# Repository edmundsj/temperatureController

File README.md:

# TEC Temperature Controller PCB
This PCB is designed to monitor and control the temperature of an object heated or cooled with a thermoelectric cooler (TEC), and is capable of driving up to 8A

## Features
- TEC temperature regulation within 0.1C using PI control
- Max TEC Voltage/current of 3.6V/6A when powered off 5V
- 1% settling time of ~90s 
- Bidirectional temp. control (heating and cooling) 
- 6A max current with 8-bit current monitoring (~25mA accuracy)
- Computer-independent measurement and temperature control using on-board interface
- Can be powered over USB (current limited by driving source)
- Closed-loop control of temperature using MCP9808 remote temperature sensor
- Two 3-digit 7-segment displays for temperature setpoint and measured value
- Knob potentiometer for setting target temperature
- Passive cooling (~4K/W thermal resistance) with 1.5" radial heatsink
- Arduino nano-based

Fully populated PCB

Unpopulated, as-fabricated PCB

## Getting Started
Kicad design files for this PCB are located in the ``kicad/`` folder. Gerbers
can be generated directly for fabrication, or you can find the latest gerbers
in the ``gerbers/`` directory. The parts required can be found in ``bom.csv``.
Software can be found in the ``controller_software/`` directory, which can be
copied to your local machine, and uploaded to an Arduino nano via the Arduino
IDE. This system is rated to work at 5V, so make sure the power adapter used is
rated for 5V, and as much current as is required. For the TEC I built this
system around, that is ~6A.

## Issues
### Issues in Version 1
- [FIXED v2] Need VDD, GND connections on header going to MCP9808 board in addition to SDA and SCL.
- [FIXED v2] Need to make sure the ordering and connector matches that of the device PCB.
- [FIXED v2] In the future, a couple of accessible header GND connections would be nice, even just for probing.
- [FIXED v2] Should edit the silkscreen to include the directionality of the Arduino Nano's USB. 
- [FIXED v2] Should swap out MOSFET for a more linear BJT
- [FIXED v2] Swap out MOSFET for transistor with much lower thermal resistance
- [FIXED v2] My choice of resistor is not sufficient, the thing heats up and starts to smoke after a couple seconds at ~5A. 

### Issues in Version 2
- [FIXED v3] R4 is too close to the heatsink, difficult to access. Moved.
- [FIXED v3] Added capacitor for filtering of input drive voltage
- [FIXED v3] Added 2x2 ground header pins for probing
- [FIXED v3] Added relay with drive transistor to allow bidirectional current flow through TEC
- [FIXED v3] Added silkscreen + courtyard + mounting holes for main heatsink
- [FIXED v3] Current sensing is unreliable due to ADC being near rails, added opamp buffer + biasing

### Issues in Version 3
- Standoffs should be as far to the outside to avoid tipping the board when using screw terminals
- Need to add test piont for VDR_F. 
- C4 should be removed. We have no business filtering a voltage going to the base of the BJT.
- Add probe points for communication interface for easier debugging. 
- Add probe points for ground silkscreen
- Decouple VDD of arduino and TEC.

## Acknowledgements

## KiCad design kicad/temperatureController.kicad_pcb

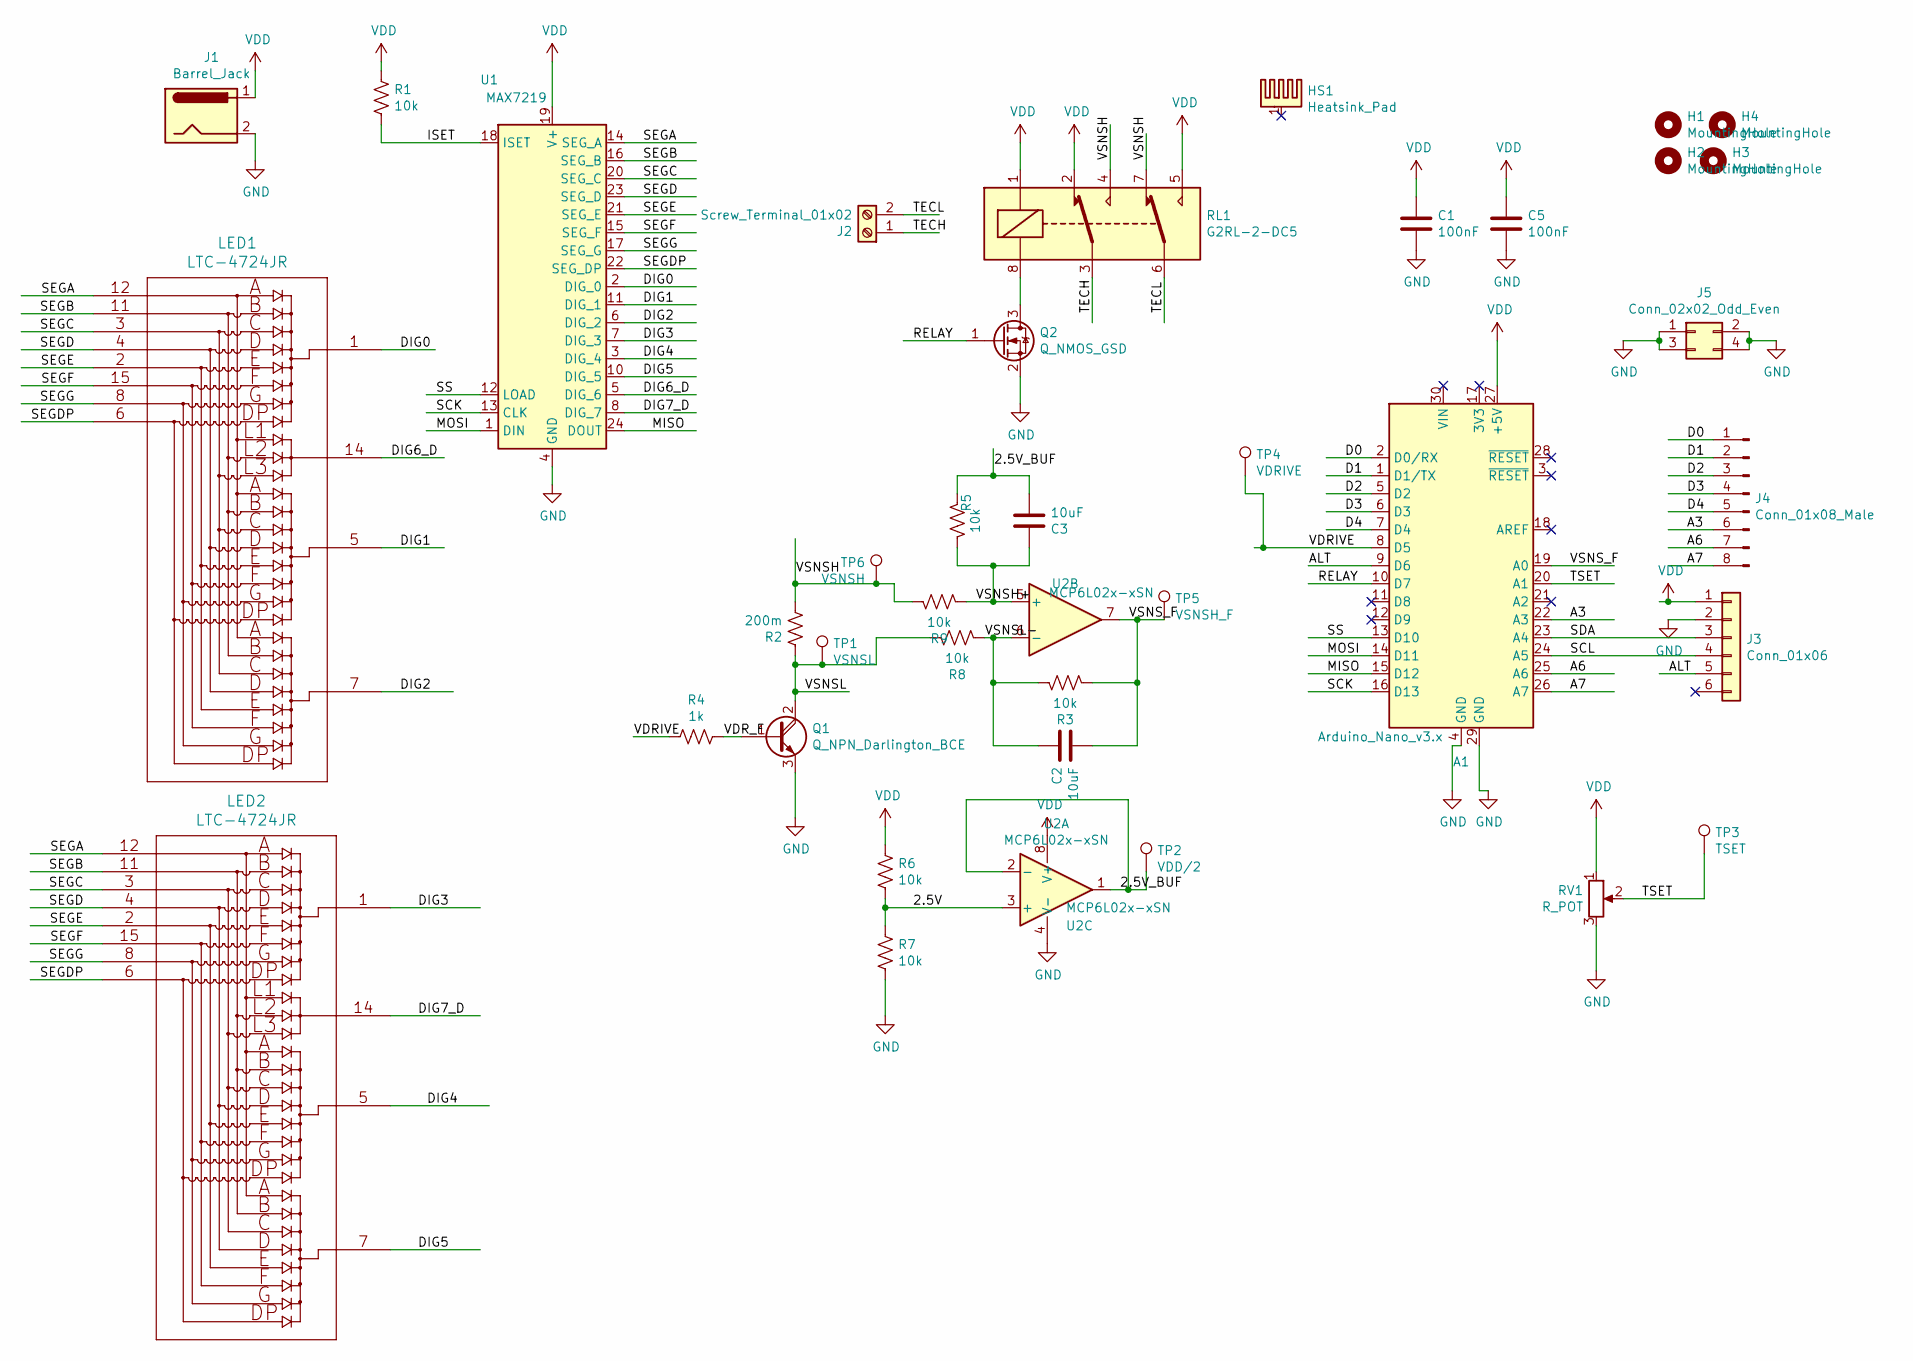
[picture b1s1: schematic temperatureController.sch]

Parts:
A1: Arduino_Nano_v3.x; Arduino_Nano
C1: 100nF; CP_Radial_D10.0mm_P5.00mm
C2, C3: 10uF; C_0805_2012Metric_Pad1.15x1.40mm_HandSolder
C5: 100nF; C_0805_2012Metric_Pad1.15x1.40mm_HandSolder
H1, H2, H3, H4: MountingHole; m3_mounting_hole
HS1: Heatsink_Pad; heatsink
J1: Barrel_Jack; BarrelJack_Horizontal
J2: Screw_Terminal_01x02; TerminalBlock_Altech_AK300-2_P5.00mm
J3: Conn_01x06; S6B-XH-SM4-TB
J4: Conn_01x08_Male; PinHeader_1x08_P2.54mm_Vertical
J5: Conn_02x02_Odd_Even; PinHeader_2x02_P2.54mm_Vertical
LED1, LED2: LTC-4724JR
Q1: Q_NPN_Darlington_BCE; TO-220-3_Vertical
Q2: Q_NMOS_GSD; SOT-323_SC-70_Handsoldering
R1, R3, R5, R6, R7, R8, R9: 10k; R_0805_2012Metric_Pad1.15x1.40mm_HandSolder
R2: 200m; TO-220_resistor
R4: 1k; R_0805_2012Metric_Pad1.15x1.40mm_HandSolder
RL1: G2RL-2-DC5; Relay_DPDT_Omron_G2RL
RV1: R_POT; P120PK_Potentiometer
TP1: VSNSL; TestPoint_Keystone_5000-5004_Miniature
TP2: VDD/2; TestPoint_Keystone_5000-5004_Miniature
TP3: TSET; TestPoint_Keystone_5000-5004_Miniature
TP4: VDRIVE; TestPoint_Keystone_5000-5004_Miniature
TP5: VSNSH_F; TestPoint_Keystone_5000-5004_Miniature
TP6: VSNSH; TestPoint_Keystone_5000-5004_Miniature
U1: MAX7219; SOIC-24W_7.5x15.4mm_P1.27mm
U2: MCP6L02x-xSN; SOIC-8_3.9x4.9mm_P1.27mm

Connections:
/2.5V: R6.2, R7.1, U2.3 (+)
/2.5V_BUF: C3.2, R5.2, TP2.1, U2.1, U2.2 (-)
/A3: A1.22 (A3), J4.6
/A6: A1.25 (A6), J4.7
/A7: A1.26 (A7), J4.8
/ALT: A1.9 (D6), J3.5
/D0: A1.2 (D0/RX), J4.1
/D1: A1.1 (D1/TX), J4.2
/D2: A1.5 (D2), J4.3
/D3: A1.6 (D3), J4.4
/D4: A1.7 (D4), J4.5
/DIG0: LED1.1, U1.2 (DIG_0)
/DIG1: LED1.5, U1.11 (DIG_1)
/DIG2: LED1.7, U1.6 (DIG_2)
/DIG3: LED2.1, U1.7 (DIG_3)
/DIG4: LED2.5, U1.3 (DIG_4)
/DIG5: LED2.7, U1.10 (DIG_5)
/DIG6_D: LED1.14, U1.5 (DIG_6)
/DIG7_D: LED2.14, U1.8 (DIG_7)
/ISET: R1.2, U1.18 (ISET)
/MISO: A1.15 (D12), U1.24 (DOUT)
/MOSI: A1.14 (D11), U1.1 (DIN)
/RELAY: A1.10 (D7), Q2.1 (G)
/SCK: A1.16 (D13), U1.13 (CLK)
/SCL: A1.24 (A5), J3.4
/SDA: A1.23 (A4), J3.3
/SEGA: LED1.12, LED2.12, U1.14 (SEG_A)
/SEGB: LED1.11, LED2.11, U1.16 (SEG_B)
/SEGC: LED1.3, LED2.3, U1.20 (SEG_C)
/SEGD: LED1.4, LED2.4, U1.23 (SEG_D)
/SEGDP: LED1.6, LED2.6, U1.22 (SEG_DP)
/SEGE: LED1.2, LED2.2, U1.21 (SEG_E)
/SEGF: LED1.15, LED2.15, U1.15 (SEG_F)
/SEGG: LED1.8, LED2.8, U1.17 (SEG_G)
/SS: A1.13 (D10), U1.12 (LOAD)
/TECH: J2.1, RL1.3
/TECL: J2.2, RL1.6
/TSET: A1.20 (A1), RV1.2, TP3.1
/VDRIVE: A1.8 (D5), R4.2, TP4.1
/VDR_F: Q1.1 (B), R4.1; also elsewhere on the board
/VSNSH: R2.2, R9.2, RL1.4, RL1.7, TP6.1
/VSNSH+: C3.1, R5.1, R9.1, U2.5 (+)
/VSNSL: Q1.2 (C), R2.1, R8.2, TP1.1
/VSNSL-: C2.1, R3.2, R8.1, U2.6 (-)
/VSNS_F: A1.19 (A0), C2.2, R3.1, TP5.1, U2.7
GND: A1.4 (GND), A1.29 (GND), C1.2, C5.2, J1.2, J3.2, J5.1, J5.2, J5.3, J5.4, Q1.3 (E), Q2.2 (S), R7.2, RV1.3, U1.4 (GND), U1.9 (GND), U2.4 (V-); also elsewhere on the board
unnamed: Q2.3 (D), RL1.8
VDD: A1.27 (+5V), C1.1, C5.1, J1.1, J3.1, R1.1, R6.1, RL1.1, RL1.2, RL1.5, RV1.1, U1.19 (V+), U2.8 (V+)

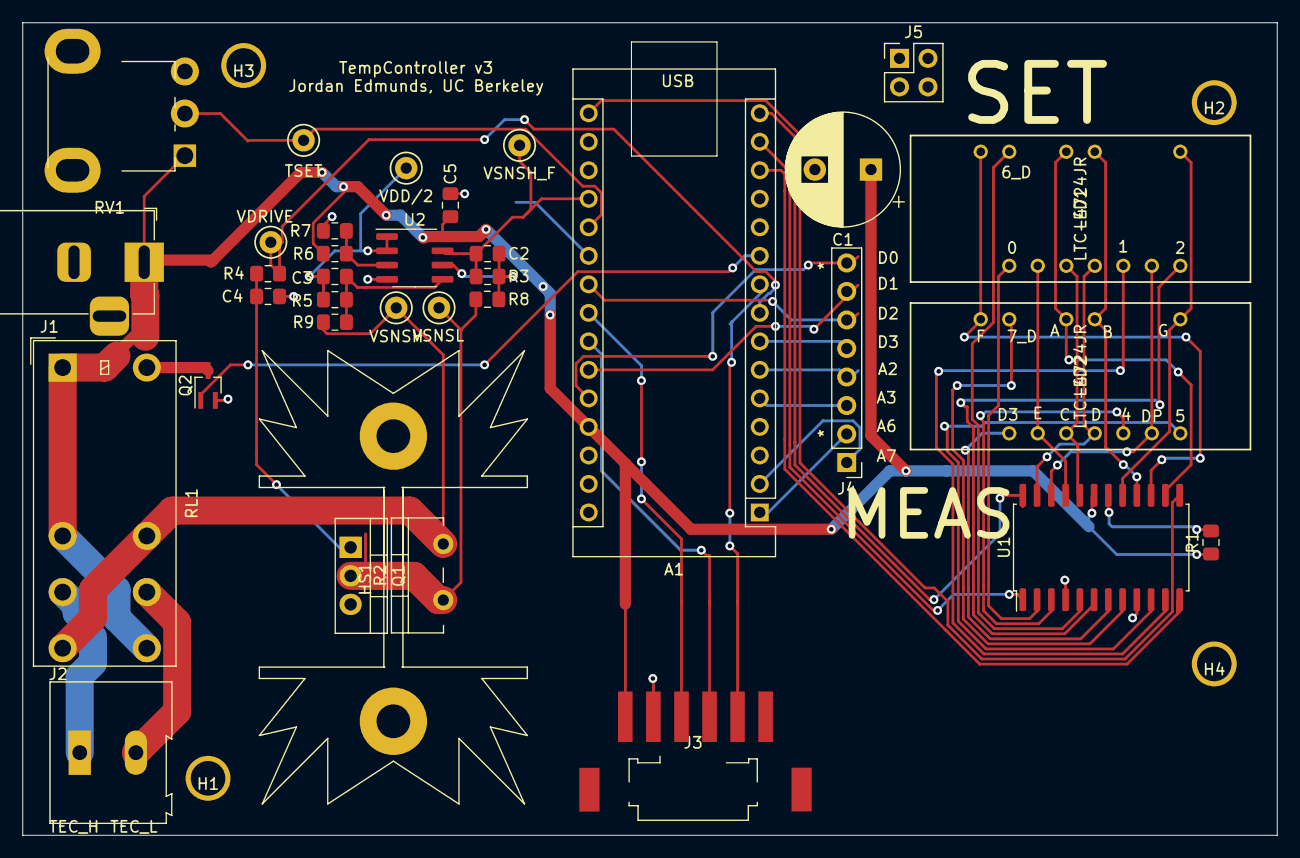
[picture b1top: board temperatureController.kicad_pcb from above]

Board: 2 copper layers, 111.8 x 72.4 mm, 39 parts (0 on the bottom side), 48 nets.

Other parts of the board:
C4: 10uF; C_0805_2012Metric_Pad1.15x1.40mm_HandSolder

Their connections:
/VDR_F: C4.1; also elsewhere on the board
GND: C4.2; also elsewhere on the board

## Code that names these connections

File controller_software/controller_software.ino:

#include <SPI.h>
#include "Seeed_MCP9808.h"
#include "displays.h"
#include <elapsedMillis.h>
#include "nano_scpi_2.h"

elapsedMillis display_time_elapsed;
elapsedMillis measurement_time_elapsed;

Display setpoint_display(DIGIT0_REGISTER, DIGIT1_REGISTER, DIGIT2_REGISTER);
Display actual_display(DIGIT3_REGISTER, DIGIT4_REGISTER, DIGIT5_REGISTER);

void setup() {
  // put your setup code here, to run once:
  pinMode(CHIP_SELECT_PIN, OUTPUT);
  pinMode(DRIVE_PIN, OUTPUT);
  pinMode(TSET_PIN, INPUT);
  pinMode(ISNS_HIGH, INPUT);
  pinMode(RELAY_PIN, OUTPUT);
  pinMode(ALT_PIN, INPUT);
    
  SPI.begin();
  Serial.begin(115200);

  // Setup the tempertature sensor interface
  initializeDisplayDriver();
  scpi.initialize();
}

void loop() {
  if(measurement_time_elapsed > SCPI::controller.sampling_time_ms) {
    SCPI::controller.control(); // chooses between temp, current, and voltage
    measurement_time_elapsed = 0;
  }

  if(display_time_elapsed > DISPLAY_REFRESH_PERIOD) {
    if(SCPI::remote_control == false) { 
      SCPI::controller.get_potentiometer_setpoint(); // gets the setpoint based on the current mode
    }
    
    setpoint_display.writeTemperature(SCPI::controller.temperature_setpoint);
    actual_display.writeTemperature(SCPI::controller.measured_temperature);
    display_time_elapsed = 0;
  }    
  if(Serial.available()) {
    SCPI::parser.ProcessInput(Serial, "\n");
  }
}

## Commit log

2021-01-05 first commit. First version to be fabricated
2021-01-13 added software for version 1 of PCB. Works well to control current for low currents, but thermal runaway makes the whole thing stop working
2021-01-13 updated PCB to include 60x lower thermal resistance transistor. Added space for heatsink, rearranged some components. Added 6-pin connector for temperature readout
2021-01-13 added gerbers for temp controller v2
2021-01-15 updated software to contain temperature sensor code
2021-01-15 updated README with features, some test data
2021-01-19 updated README with features to make the thing readable
2021-01-23 added debugging information to README. Implemented closed-loop temperature control, tuned PI controller to have 30% overshoot and decent transient response. optimal choice of Ti might be slightly lon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
2021-01-24 updated PCB with a relay, signal conditioning for sense resistor output. Ready to fabricate
2021-01-24 updated README, bill of materials with new components and capabilities. Fixed PCB to have a differential amplifier to properly bias the nano's ADC.
2021-01-29 updated all gerbers for version 3 of PCB. This version will be fabricated by AllPCB
2021-02-12 tested version 3, works for bidirectional current control up to 4.6A, corresponding to a dT of 15C when one side is attached to a heatsink and actively cooled.
2021-03-02 updated controller to respond to SCPI commands for use by external python interface as needed
2021-03-08 renamed files, moved to appropriate locations
2021-03-08 added PCB images, basic getting started documentation. Modified features, added DEBUGGING markdown document
2021-03-08 fixed README bug
2021-03-08 fixed more README bugs
2022-02-16 updated arduino software, README

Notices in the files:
parts and their libraries:
Copyright 2016 Accelerated Designs. All rights reserved.
